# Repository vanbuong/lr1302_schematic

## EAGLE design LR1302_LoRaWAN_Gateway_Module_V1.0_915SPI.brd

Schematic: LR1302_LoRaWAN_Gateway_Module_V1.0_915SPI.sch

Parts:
ANT1: U.FL_SMTU.FL-R-SMD; U.FL-R-SMD
ANT2: NC; U.FL-R-SMD
C1, C3, C5, C7, C9, C10, C11, C12, C13, C17, C23, C63, C72, C79, C81, C82, C84: 100nF; C0402
C2, C4, C6, C8, C14, C20: 1uF; C0402
C15, C21, C29, C40: 10pF; C0402
C16, C22: 470nF; C0402
C18, C19, C24, C25: 3.6pF; C0402
C26: 47nF; C0402
C27: 47pF; C0402
C28, C41, C43, C46, C48, C49, C50, C54, C55, C56, C57, C58, C59, C60, C61, C64, C65, C66, C67, C68, C69, C71, C80: NC; C0402
C30: 39pF; C0402
C31: 2.7pF; C0402
C33, C34, C47, C51, C52, C53: 56pF; C0402
C35, C62, C78, C83: 4.7uF; C0603
C36: 10nF; C0402
C37: 1nF; C0402
C38: 120pF; C0402
C39: 33pF; C0402
C42: 2.4pF; C0402
C44: 1.8pF; C0402
C45: 2.1pF; C0402
C73: 2.2uF; C0402
C74, C75, C76, C77: 22uF; C0603
D1: BLUE; LED-0402
D2: RED; LED-0402
D3, D5: GREEN; LED-0402
D4: BAT54XV2T1G; D_SOD523
D6: NC; D0402
D8: LXES15AAA1-153; D0402
FB1, FB3, FB5, FB6: FB; L0402
J1: PCI-EXPRESS-CARD-P52; PCIE-MINI-S52
J2, J11: PAD-THO-2.65MM; PAD-THO-2.6*5MM
J3, J4, J5, J6, J7, J10, J17: PBJ-ICSRC6508-SMD
L1, L4: 15uH; L0805
L2, L5, L16, L17, L19: NC; L0402
L3, L6: 12nH; L0402
L7: 47nH; L0402
L8: 2.5nH; L0402
L9, L15: 4.7nH; L0402
L10: 1.2nH; L0402
L11: 6.8nH; L0402
L12: 2.7nH; L0402
L13: 7.5nH; L0402
L14: 3.3nH; L0402
L18: NC; L0805
L20: 2.2uH; L3015_SMD
P1, P2, P3, P4, P5, P6, P7, P8, P9, P10, P11, P12, P13, P14, P15, P16, P17, P18, P19, P20, P21, P23, P24: TEST_PADPAD-1.0MM; TEST_PAD-1.0MM
Q1: CJ2101; MOS_SOT323
Q2: CJ2102; MOS_SOT323
R1, R4, R5, R48: 47K; R0402
R2, R18, R33, R34, R35: 100R; R0402
R3, R7, R9, R32, R36, R37, R38, R39, R40, R41, R42, R43, R44, R45, R53, R57, R58: NC; R0402
R8, R10, R11, R12, R13, R14, R15, R16, R24, R25, R27, R31: 0R; R0402
R17: 10K; R0402
R19, R20, R46, R47: 4.7K; R0402
R21: 3.3K; R0402
R22: 2K; R0402
R23, R51: 680R; R0402
R26, R28: 220R; R0402
R49, R50: 59K 1%; R0402
R52: 100K; R0402
R54: 10R; R0402
U1: SX1302IMLTRT; QFN68-7*7MM
U2, U3: SX1250IMLTRT; QFN24-4*4MM
U4, U5, U12: TA0281A-SAW-915MHZ; SAW-SMD6-3*3MM
U6: SKY66420-11; MCM-16-EP(3X3)
U8: NC; QFN24-4*4MM
U9: NC; UFQFPN-32-5*5MM
U10: STTS751; UDFN-6(2X2)
U11: MT3520B; IC_SOT23-5
Y1: NC; XATL-3215-SMD
Y2: TCXO-32MHZ; TXCO-SMD2.0*1.6

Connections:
1V2: C76.2, C77.2, C78.2, FB3.1, L20.2, R49.1
3V3_MAIN: C62.2, C64.2, C65.2, C68.2, C69.2, C71.2, C72.2, C73.2, C74.2, C75.2, FB5.1, FB6.1, J1.2 (3V3), J1.24 (3V3), J1.39 (3V3), J1.41 (3V3), J1.52 (3V3), P7.P$1, Q1.2 (S), R17.2, R44.2, R46.2, R47.2, R48.2, R51.1, R57.2, U9.1 (VDD), U9.5 (VDDA), U9.17 (VDD), U10.3 (VDD), U11.1 (EN), U11.4 (VIN)
CONFIG_OK: R22.1, U1.66 (GPIO[0])
CSD: C51.1, R33.2, U6.4 (CSD)
D+: J1.38, P2.P$1, R9.1
D-: J1.36, P1.P$1, R7.1
GND: ANT1.2 (GND), ANT1.3 (GND), ANT2.2 (GND), ANT2.3 (GND), C1.1, C2.1, C3.1, C4.1, C5.1, C6.1, C7.1, C8.1, C9.1, C10.1, C11.1, C12.1, C13.1, C14.2, C16.2, C17.1, C18.1, C20.2, C22.2, C23.1, C24.1, C26.2, C27.2, C29.2, C31.2, C35.1, C36.1, C37.1, C38.1, C39.1, C40.1, C41.1, C42.1, C43.1, C44.1, C46.1, C48.1, C49.1, C51.2, C52.2, C53.2, C54.2, C56.2, C57.1, C58.1, C60.1, C62.1, C64.1, C65.1, C66.1, C67.2, C68.1, C69.1, C71.1, C72.1, C73.1, C74.1, C75.1, C76.1, C77.1, C78.1, C79.1, C80.1, C81.1, C82.1, C83.1, C84.1, D1.2 (-), D2.2 (-), D3.2 (-), D5.2 (-), D6.2, D8.2, J1.4 (GND), J1.9 (GND), J1.15 (GND), J1.18 (GND), J1.21 (GND), J1.26 (GND), J1.27 (GND), J1.29 (GND), J1.34 (GND), J1.35 (GND), J1.37 (GND), J1.40 (GND), J1.43 (GND), J1.50 (GND), J2.1, J3.1, J3.2, J3.3, J4.1, J4.2, J4.3, J5.1, J5.2, J5.3, J6.1, J6.2, J6.3, J7.1, J7.2, J7.3, J10.1, J10.2, J10.3, J11.1, J17.1, J17.2, J17.3, P8.P$1, P24.P$1, Q2.2 (S), R3.1, R3.2, R5.1, R15.1, R15.2, R16.1, R16.2, R43.2, R45.1, R50.2, R52.2, R53.1, R53.2, U1.6 (GND), U1.9 (GND), U1.15 (GND), U1.20 (SP_VALID), U1.24 (GND), U1.25 (GND), U1.39 (GND), U1.46 (GND), U1.55 (GND), U1.62 (GND), U1.69 (GND), U2.7 (GND), U2.20 (GND), U2.25 (GND), U3.7 (GND), U3.20 (GND), U3.25 (GND), U4.1 (GND), U4.3 (GND), U4.4 (GND), U4.6 (GND), U5.1 (GND), U5.3 (GND), U5.4 (GND), U5.6 (GND), U6.10 (GND), U6.12 (GND), U6.17 (GND), U8.2 (GND), U8.5 (GND), U8.8 (GND), U8.20 (GND), U8.25 (GND), U9.16 (VSS), U9.32 (VSS), U9.33 (VSS), U10.4 (ADDR/T\H\E\R\M\), U10.5 (GND), U11.2 (GND), U12.1 (GND), U12.3 (GND), U12.4 (GND), U12.6 (GND), Y2.1 (GND), Y2.2 (GND)
GPIO6: U1.57 (GPIO[6])
GPIO9: U1.52 (GPIO[9])
GPIO10: R19.1, U1.51 (GPIO[10])
GPIO11: R20.1, U1.50 (GPIO[11])
HOST_CSN: P12.P$1, R1.1, R13.1, U1.1 (HOST_CSN), U9.10 (PA4)
HOST_MISO: P10.P$1, R2.2, R11.1, R38.1, U9.12 (PA6)
HOST_MOSI: P11.P$1, R12.1, U1.3 (HOST_MOSI), U8.17 (MOSI), U9.13 (PA7)
HOST_SCK: P9.P$1, R10.1, U1.4 (HOST_SCK), U8.18 (SCK), U9.11 (PA5)
I2C_SCL: J1.30, P16.P$1, R47.1, U9.29 (PB6), U10.1 (SCL)
I2C_SDA: J1.32, P19.P$1, R46.1, U9.30 (PB7), U10.6 (SDA)
MCU_NRESET: C80.2, P6.P$1, R57.1, R58.1, U9.4 (NRST)
unnamed: R2.1, U1.2 (HOST_MISO)
unnamed: J1.45, R10.2
unnamed: R8.1, U1.34 (RADIO_B_CLK_I)
unnamed: J1.47, R11.2
unnamed: J1.49, R12.2
unnamed: J1.51, R13.2
unnamed: C63.1, R54.1
unnamed: R14.1, U1.43 (RADIO_A_CLK_I)
unnamed: Q1.1 (G), Q2.3 (D), R17.1
unnamed: Q2.1 (G), R18.1, R52.1
unnamed: D3.1 (+), R23.2
unnamed: D2.1 (+), R22.2
unnamed: D1.1 (+), R21.2
unnamed: C13.2, FB1.2, Y2.4 (VCC)
unnamed: R24.1, Y2.3 (OUT)
unnamed: L1.2, U2.8 (DCC_SW)
unnamed: C14.1, L2.2, R25.1, U2.2 (VDD_IN)
unnamed: C16.1, L1.1, L2.1, U2.6 (VREG)
unnamed: C15.2, U2.3 (XTA)
unnamed: C15.1, R26.1
unnamed: C18.2, L3.1, U2.22 (RFI_P)
unnamed: C19.2, L3.2, U2.23 (RFI_N)
unnamed: C28.2, L7.1, L8.1, U3.24 (RFO)
unnamed: C20.1, L5.2, R27.1, U3.2 (VDD_IN)
unnamed: L4.2, U3.8 (DCC_SW)
unnamed: C22.1, L4.1, L5.1, U3.6 (VREG)
unnamed: C21.2, U3.3 (XTA)
unnamed: C21.1, R28.1
unnamed: C24.2, L6.1, U3.22 (RFI_P)
unnamed: C25.2, L6.2, U3.23 (RFI_N)
unnamed: C30.2, L9.1
unnamed: C31.1, L9.2, U12.2 (IN/OUT)
unnamed: C28.1, C29.1, C30.1, L8.2
unnamed: C33.1, U12.5 (OUT/IN)
unnamed: C19.1, C25.1, C61.1, U4.5 (OUT/IN)
unnamed: C34.1, U4.2 (IN/OUT)
unnamed: C33.2, U6.1 (TX)
unnamed: C34.2, U6.2 (RX)
unnamed: L10.1, U6.16 (VCC1)
unnamed: U5.5 (OUT/IN), U6.7 (LNA_IN)
unnamed: L11.1, L12.1, U6.13 (PA_OUT)
unnamed: C40.2, C41.2, L12.2, L13.1
unnamed: C42.2, L13.2, U6.11 (TX_IN)
unnamed: C43.2, C45.2, L14.1, U6.9 (ANT)
unnamed: C44.2, C45.1, L14.2, L15.1
unnamed: C46.2, C47.2, L15.2
unnamed: ANT1.1 (SIGNAL), C47.1, D8.1
unnamed: R31.1, U6.8 (RX_FLT)
unnamed: C54.1, L17.2, R36.1, U8.1 (VDD_IN)
unnamed: R31.2, R32.1, U5.2 (IN/OUT)
unnamed: C55.1, R37.1
unnamed: C49.2, C50.2, L16.2
unnamed: ANT2.1 (SIGNAL), C50.1, D6.1
unnamed: C48.2, L16.1, R32.2
unnamed: C55.2, U8.3 (XTA)
unnamed: L18.2, U8.9 (DCC_SW)
unnamed: C56.1, L17.1, L18.1, U8.7 (VREG)
unnamed: R38.2, U8.16 (MISO)
unnamed: C58.2, L19.1, U8.21 (RFI_P)
unnamed: C59.2, L19.2, U8.22 (RFI_N)
unnamed: C59.1, C60.2, C61.2
unnamed: R41.2, U8.19 (NSS)
unnamed: R42.2, R43.1, U9.6 (PA0-CK_IN)
unnamed: C67.1, U9.3 (PC15-OSC32_OUT), Y1.1
unnamed: C66.2, U9.2 (PC14-OSC32_IN), Y1.2
unnamed: R48.1, U10.2 (\E\V\E\N\T\)
unnamed: D5.1 (+), R51.2
unnamed: L20.1, U11.3 (SW)
unnamed: R44.1, R45.2, U9.31 (BOOT)
unnamed: R49.2, R50.1, U11.5 (FB)
PA_ON: C53.1, R35.2, U6.5 (CPS)
POWER_EN: U9.7 (PA1)
PPS: J1.19, P21.P$1, U1.8 (PPS), U9.27 (PB4)
P_RESET: D4.+, J1.22, P20.P$1, R58.2
RADIO_A_CLK_32M: R14.2, R42.1, U3.14 (BUSY)
RADIO_A_CLK_O: U1.48 (RADIO_A_IQ[4]), U3.11 (DIO5)
RADIO_A_CSN: U1.68 (RADIO_A_CSN), U3.19 (NSS)
RADIO_A_IQ0: U1.44 (RADIO_A_IQ[0]), U3.13 (DIO1)
RADIO_A_IQ1: U1.45 (RADIO_A_IQ[1]), U3.12 (DIO2)
RADIO_A_IQ2: U1.49 (RADIO_A_IQ[2]), U3.5 (DIO3)
RADIO_A_IQ3: U1.41 (RADIO_A_IQ[3]), U3.21 (DIO4)
RADIO_A_MISO: U1.42 (RADIO_A_MISO), U3.16 (MISO_TX)
RADIO_A_MOSI: U1.67 (RADIO_A_MOSI), U3.17 (MOSI_RX)
RADIO_A_NRESET: U1.13 (RADIO_CTRL[3]), U3.15 (NRESET)
RADIO_A_SCK: U1.65 (RADIO_A_SCK), U3.18 (SCK)
RADIO_B_CLK_32M: R8.2, U2.14 (BUSY)
RADIO_B_CLK_O: U1.37 (RADIO_B_IQ[4]), U2.11 (DIO5)
RADIO_B_CSN: U1.18 (RADIO_B_CSN), U2.19 (NSS)
RADIO_B_IQ0: U1.35 (RADIO_B_IQ[0]), U2.13 (DIO1)
RADIO_B_IQ1: U1.36 (RADIO_B_IQ[1]), U2.12 (DIO2)
RADIO_B_IQ2: U1.38 (RADIO_B_IQ[2]), U2.5 (DIO3)
RADIO_B_IQ3: U1.32 (RADIO_B_IQ[3]), U2.21 (DIO4)
RADIO_B_MISO: U1.33 (RADIO_B_MISO), U2.16 (MISO_TX)
RADIO_B_MOSI: U1.19 (RADIO_B_MOSI), U2.17 (MOSI_RX)
RADIO_B_NRESET: U1.28 (RADIO_CTRL[9]), U2.15 (NRESET)
RADIO_B_SCK: U1.21 (RADIO_B_SCK), U2.18 (SCK)
RADIO_CTRL1: U1.11 (RADIO_CTRL[1])
RXTX_SW: C52.1, R34.2, U6.6 (CTX)
RX_ON: R21.1, U1.59 (GPIO[4])
SWCLK: P3.P$1, U9.24 (PA14)
SWDIO: P4.P$1, U9.23 (PA13)
SX1261_BUSY: J1.8, P17.P$1, U8.14 (BUSY), U9.9 (PA3)
SX1261_DIO1: J1.33, P15.P$1, U1.54 (GPIO[7]), U8.13 (DIO1), U9.15 (PB1)
SX1261_DIO2: J1.31, P14.P$1, U8.12 (DIO2)
SX1261_DIO3: P5.P$1, U8.6 (DIO3)
SX1261_NRESET: J1.10, P18.P$1, R40.1, U8.15 (NRESET), U9.18 (PA8)
SX1261_NSS: J1.25, P13.P$1, R39.1, R41.1, U9.14 (PB0)
SX1302_CSD: R4.1, R33.1, U1.10 (RADIO_CTRL[0])
SX1302_GPIO8: U1.53 (GPIO[8]), U9.26 (PB3)
SX1302_PA_ON: R35.1, U1.16 (RADIO_CTRL[4])
SX1302_RESET: C63.2, D4.-, R5.2, U1.7 (RESET), U9.8 (PA2)
SX1302_RXTX_SW: R34.1, U1.12 (RADIO_CTRL[2])
TCXO_32M_O: R24.2, R26.2, R28.2, R37.2
TX_ON: R23.1, U1.63 (GPIO[2])
USB_D+: R9.2, U9.22 (PA12)
USB_D-: R7.2, U9.21 (PA11)
VCCIO33: C3.2, C4.2, C7.2, C8.2, C10.2, C12.2, C83.2, C84.2, Q1.3 (D), R1.2, R4.2, R19.2, R20.2, R54.2, U1.14 (VCC_IO), U1.30 (VCC_IO), U1.47 (VCC_IO), U1.61 (VCC_IO)
VCC_FEM: C35.2, C36.2, C37.2, C38.2, C39.2, C82.2, FB6.2, L10.2, L11.2, U6.15 (VCC0)
VCORE12: C1.2, C2.2, C5.2, C6.2, C9.2, C11.2, C79.2, FB3.2, P23.P$1, R18.2, U1.5 (VCC_CORE), U1.23 (VCC_CORE), U1.40 (VCC_CORE), U1.56 (VCC_CORE)
VDD_RADIO: C17.2, C23.2, C57.2, C81.2, FB1.1, FB5.2, R25.2, R27.2, R36.2, R39.2, R40.2, U2.9 (VBAT_RF), U2.10 (VBAT_DIO), U3.9 (VBAT_RF), U3.10 (VBAT_DIO), U8.10 (VBAT), U8.11 (VBAT_IO)
VR_PA: C26.1, C27.1, L7.2, U3.1 (VR_PA)

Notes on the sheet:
TA0281A-SAW-915MHZ
868M
915M
SPI
USB

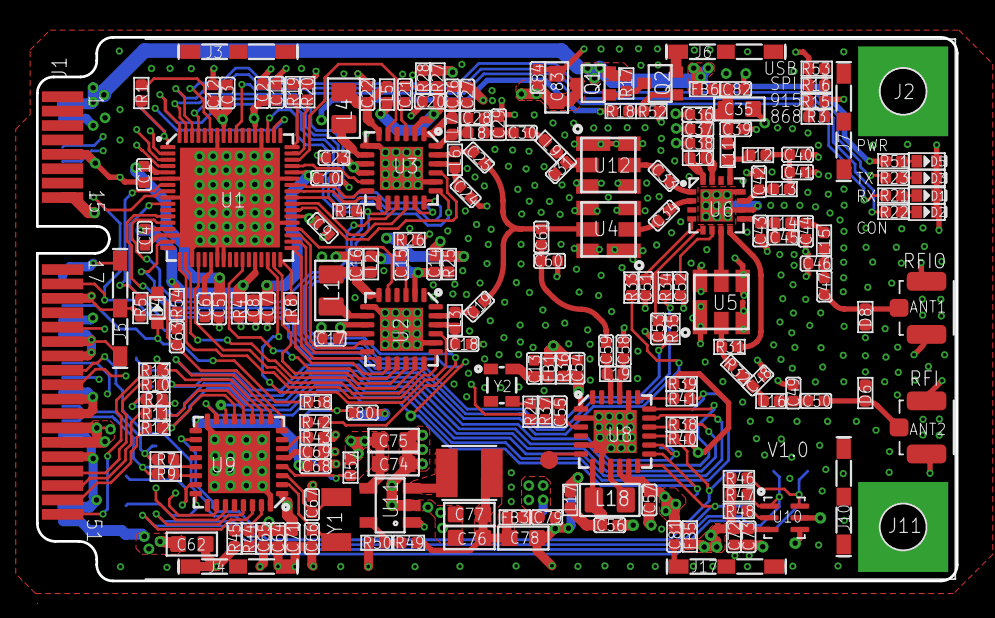
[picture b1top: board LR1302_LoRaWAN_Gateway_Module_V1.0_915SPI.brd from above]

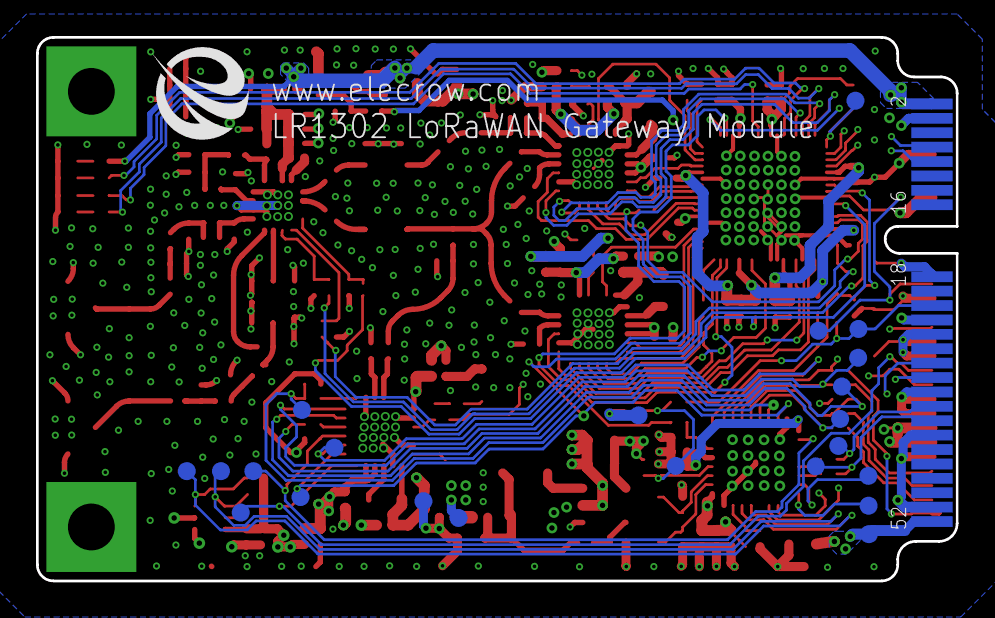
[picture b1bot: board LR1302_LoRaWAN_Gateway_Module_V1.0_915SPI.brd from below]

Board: 4 copper layers, 51.1 x 30.2 mm, 217 parts (23 on the bottom side), 135 nets.

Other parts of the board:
U$160: ELECROW-NEW
